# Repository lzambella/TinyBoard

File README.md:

40% keyboard based on a layout I found somewhere, possibly Reddit, and modified for my own tastes. Runs on TMK firmware.

**Switches**
Uses any Cherry full size 5-hole compatible ones. I like to use Gateron North Poles.

LEDs should be 1206 package.

TODO:
* Add STEP files for 3d printing/designing
* PDF files of schematics
* Better docs
* images
* how to build one?

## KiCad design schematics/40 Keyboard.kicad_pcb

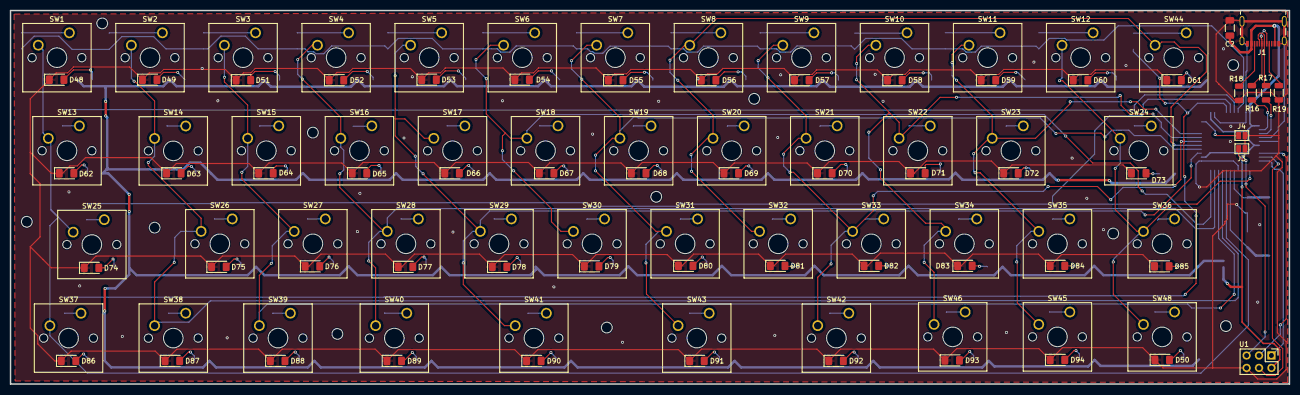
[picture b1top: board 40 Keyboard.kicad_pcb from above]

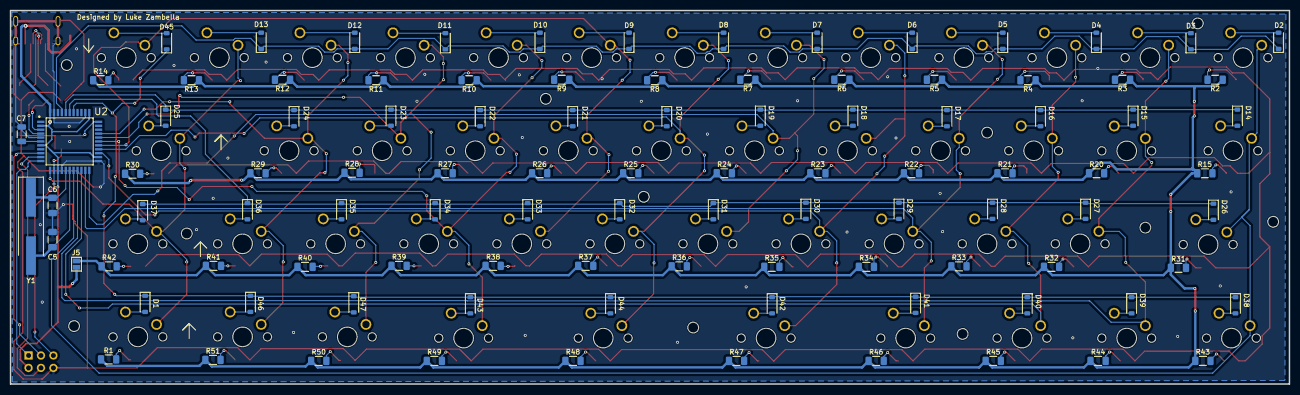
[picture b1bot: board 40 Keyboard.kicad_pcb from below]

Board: 2 copper layers, 261.1 x 76.2 mm, 203 parts (100 on the bottom side), 127 nets.

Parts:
C2: 4.7uF; C_1206_3216Metric_Pad1.33x1.80mm_HandSolder
C5, C6: C1206C220K3HAC7800; C_1206_3216Metric_Pad1.33x1.80mm_HandSolder
C7: 1uF; C_1206_3216Metric
D1, D2, D3, D4, D5, D6, D7, D8, D9, D10, D11, D12, D13, D14, D15, D16, D17, D18, D19, D20, D21, D22, D23, D24, D25, D26, D27, D28, D29, D30, D31, D32, D33, D34, D35, D36, D37, D38, D39, D40, D41, D42, D43, D44, D45, D46, D47: D; D_SOD-123
D48, D49, D50, D51, D52, D53, D54, D55, D56, D57, D58, D59, D60, D61, D62, D63, D64, D65, D66, D67, D68, D69, D70, D71, D72, D73, D74, D75, D76, D77, D78, D79, D80, D81, D82, D83, D84, D85, D86, D87, D88, D89, D90, D91, D92, D93, D94: LED; LED_1206_3216Metric_Pad1.42x1.75mm_HandSolder
J1: 2171790001; MOLEX_2171790001
J3: RESET; SolderJumper-2_P1.3mm_Open_Pad1.0x1.5mm
J4: HWB; SolderJumper-2_P1.3mm_Open_Pad1.0x1.5mm
J5: LED_ENABLE_JUMPER; SolderJumper-2_P1.3mm_Open_Pad1.0x1.5mm
R1, R2, R3, R4, R5, R6, R7, R8, R9, R10, R11, R12, R13, R14, R15, R20, R21, R22, R23, R24, R25, R26, R27, R28, R29, R30, R31, R32, R33, R34, R35, R36, R37, R38, R39, R40, R41, R42, R43, R44, R45, R46, R47, R48, R49, R50, R51: 511; R_1206_3216Metric_Pad1.30x1.75mm_HandSolder
R16, R17: 22; R_1206_3216Metric
R18, R19: 5.1k; R_1206_3216Metric
SW1, SW2, SW3, SW4, SW5, SW6, SW7, SW8, SW9, SW10, SW11, SW12, SW13, SW14, SW15, SW16, SW17, SW18, SW19, SW20, SW21, SW22, SW23, SW24, SW25, SW26, SW27, SW28, SW29, SW30, SW31, SW32, SW33, SW34, SW35, SW36, SW37, SW38, SW39, SW40, SW41, SW42, SW43, SW44, SW45, SW46, SW48: KS-33; Cherry MX switch
U1: PinHeader_2x03_P2.54mm_Vertical
U2: ATMEGA32U4-AU; atmega32u4
Y1: 16Mhz; Crystal_SMD_HC49-SD_HandSoldering

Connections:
32U4_USB_DN: J1.A7 (DN1), J1.B7 (DN2), R16.1
32U4_USB_DP: J1.A6 (DP1), J1.B6 (DP2), R17.1
/LED Circuit/LED_5V: J5.1, R1.1, R2.1, R3.1, R4.1, R5.1, R6.1, R7.1, R8.1, R9.1, R10.1, R11.1, R12.1, R13.1, R14.1, R15.1, R20.1, R21.1, R22.1, R23.1, R24.1, R25.1, R26.1, R27.1, R28.1, R29.1, R30.1, R31.1, R32.1, R33.1, R34.1, R35.1, R36.1, R37.1, R38.1, R39.1, R40.1, R41.1, R42.1, R43.1, R44.1, R45.1, R46.1, R47.1, R48.1, R49.1, R50.1, R51.1
/Matrix/D_C1R1: D2.2 (A), SW1.1
/Matrix/D_C1R2: D14.2 (A), SW13.1
/Matrix/D_C1R3: D26.2 (A), SW25.1
/Matrix/D_C1R4: D38.2 (A), SW37.1
/Matrix/D_C2R1: D3.2 (A), SW2.1
/Matrix/D_C2R2: D15.2 (A), SW14.1
/Matrix/D_C2R3: D27.2 (A), SW26.1
/Matrix/D_C2R4: D39.2 (A), SW38.1
/Matrix/D_C3R1: D4.2 (A), SW3.1
/Matrix/D_C3R2: D16.2 (A), SW15.1
/Matrix/D_C3R3: D28.2 (A), SW27.1
/Matrix/D_C3R4: D40.2 (A), SW39.1
/Matrix/D_C4R1: D5.2 (A), SW4.1
/Matrix/D_C4R2: D17.2 (A), SW16.1
/Matrix/D_C4R3: D29.2 (A), SW28.1
/Matrix/D_C4R4: D41.2 (A), SW40.1
/Matrix/D_C5R1: D6.2 (A), SW5.1
/Matrix/D_C5R2: D18.2 (A), SW17.1
/Matrix/D_C5R3: D30.2 (A), SW29.1
/Matrix/D_C5R4: D42.2 (A), SW41.1
/Matrix/D_C6R1: D7.2 (A), SW6.1
/Matrix/D_C6R2: D19.2 (A), SW18.1
/Matrix/D_C6R3: D31.2 (A), SW30.1
/Matrix/D_C7R1: D8.2 (A), SW7.1
/Matrix/D_C7R2: D20.2 (A), SW19.1
/Matrix/D_C7R3: D32.2 (A), SW31.1
/Matrix/D_C7R4: D44.2 (A), SW43.1
/Matrix/D_C8R1: D9.2 (A), SW8.1
/Matrix/D_C8R2: D21.2 (A), SW20.1
/Matrix/D_C8R3: D33.2 (A), SW32.1
/Matrix/D_C8R4: D45.2 (A), SW44.1
/Matrix/D_C9R1: D10.2 (A), SW9.1
/Matrix/D_C9R2: D22.2 (A), SW21.1
/Matrix/D_C9R3: D34.2 (A), SW33.1
/Matrix/D_C9R4: D43.2 (A), SW42.1
/Matrix/D_C10R1: D11.2 (A), SW10.1
/Matrix/D_C10R2: D23.2 (A), SW22.1
/Matrix/D_C10R3: D35.2 (A), SW34.1
/Matrix/D_C10R4: D47.2 (A), SW46.1
/Matrix/D_C11R1: D12.2 (A), SW11.1
/Matrix/D_C11R2: D24.2 (A), SW23.1
/Matrix/D_C11R3: D36.2 (A), SW35.1
/Matrix/D_C11R4: D46.2 (A), SW45.1
/Matrix/D_C12R1: D13.2 (A), SW12.1
/Matrix/D_C12R2: D25.2 (A), SW24.1
/Matrix/D_C12R3: D37.2 (A), SW36.1
/Matrix/D_C12R4: D1.2 (A), SW48.1
/Microcontroller/XTAL_1: C5.1, U2.17 (XTAL1), Y1.2
/Microcontroller/XTAL_2: C6.1, U2.16 (XTAL2), Y1.1
COL_1: SW1.2, SW13.2, SW25.2, SW37.2, U2.18 (PD0)
COL_2: SW2.2, SW14.2, SW26.2, SW38.2, U2.19 (PD1)
COL_3: SW3.2, SW15.2, SW27.2, SW39.2, U2.20 (PD2)
COL_4: SW4.2, SW16.2, SW28.2, SW40.2, U2.21 (PD3)
COL_5: SW5.2, SW17.2, SW29.2, SW41.2, U2.25 (PD4)
COL_6: SW6.2, SW18.2, SW30.2, U2.22 (PD5)
COL_7: SW7.2, SW19.2, SW31.2, SW43.2, U2.26 (PD6)
COL_8: SW8.2, SW20.2, SW32.2, SW44.2, U2.27 (PD7)
COL_9: SW9.2, SW21.2, SW33.2, SW42.2, U2.28 (PB4)
COL_10: SW10.2, SW22.2, SW34.2, SW46.2, U2.29 (PB5)
COL_11: SW11.2, SW23.2, SW35.2, SW45.2, U2.30 (PB6)
COL_12: SW12.2, SW24.2, SW36.2, SW48.2, U2.12 (PB7)
GND: C2.2, C5.2, C6.2, C7.2, D48.1 (K), D49.1 (K), D50.1 (K), D51.1 (K), D52.1 (K), D53.1 (K), D54.1 (K), D55.1 (K), D56.1 (K), D57.1 (K), D58.1 (K), D59.1 (K), D60.1 (K), D61.1 (K), D62.1 (K), D63.1 (K), D64.1 (K), D65.1 (K), D66.1 (K), D67.1 (K), D68.1 (K), D69.1 (K), D70.1 (K), D71.1 (K), D72.1 (K), D73.1 (K), D74.1 (K), D75.1 (K), D76.1 (K), D77.1 (K), D78.1 (K), D79.1 (K), D80.1 (K), D81.1 (K), D82.1 (K), D83.1 (K), D84.1 (K), D85.1 (K), D86.1 (K), D87.1 (K), D88.1 (K), D89.1 (K), D90.1 (K), D91.1 (K), D92.1 (K), D93.1 (K), D94.1 (K), J1.A1B12 (GND1), J1.B1A12 (GND2), J1.SH1 (SHIELD1), J1.SH2 (SHIELD2), J1.SH3 (SHIELD3), J1.SH4 (SHIELD4), J3.1, J4.2, R18.2, R19.2, U1.6 (GND), U2.5 (UGND), U2.15 (GND), U2.23 (GND), U2.35 (GND), U2.43 (GND)
MISO: U1.1 (MISO), U2.11 (PB3)
MOSI: U1.4 (MOSI), U2.10 (PB2)
unnamed: D48.2 (A), R2.2
unnamed: D49.2 (A), R3.2
unnamed: D50.2 (A), R1.2
unnamed: D51.2 (A), R4.2
unnamed: D52.2 (A), R5.2
unnamed: D53.2 (A), R6.2
unnamed: D54.2 (A), R7.2
unnamed: D55.2 (A), R8.2
unnamed: D56.2 (A), R9.2
unnamed: D57.2 (A), R10.2
unnamed: D58.2 (A), R11.2
unnamed: D59.2 (A), R12.2
unnamed: D60.2 (A), R13.2
unnamed: D61.2 (A), R14.2
unnamed: D62.2 (A), R15.2
unnamed: D63.2 (A), R20.2
unnamed: D64.2 (A), R21.2
unnamed: D65.2 (A), R22.2
unnamed: D66.2 (A), R23.2
unnamed: D67.2 (A), R24.2
unnamed: D68.2 (A), R25.2
unnamed: D69.2 (A), R26.2
unnamed: D70.2 (A), R27.2
unnamed: D71.2 (A), R28.2
unnamed: D72.2 (A), R29.2
unnamed: D73.2 (A), R30.2
unnamed: D74.2 (A), R31.2
unnamed: D75.2 (A), R32.2
unnamed: D76.2 (A), R33.2
unnamed: D77.2 (A), R34.2
unnamed: D78.2 (A), R35.2
unnamed: D79.2 (A), R36.2
unnamed: D80.2 (A), R37.2
unnamed: D81.2 (A), R38.2
unnamed: D82.2 (A), R39.2
unnamed: D83.2 (A), R40.2
unnamed: D84.2 (A), R41.2
unnamed: D85.2 (A), R42.2
unnamed: D86.2 (A), R43.2
unnamed: D87.2 (A), R44.2
unnamed: D88.2 (A), R45.2
unnamed: D89.2 (A), R46.2
unnamed: D90.2 (A), R47.2
unnamed: D91.2 (A), R48.2
unnamed: D92.2 (A), R49.2
unnamed: D93.2 (A), R50.2
unnamed: D94.2 (A), R51.2
unnamed: J1.A5 (CC1), R19.1
unnamed: J1.B5 (CC2), R18.1
unnamed: R17.2, U2.4 (D+)
unnamed: R16.2, U2.3 (D-)
unnamed: J4.1, U2.33 (PE2)
unnamed: C7.1, U2.6 (UCAP)
ROW_1: D2.1 (K), D3.1 (K), D4.1 (K), D5.1 (K), D6.1 (K), D7.1 (K), D8.1 (K), D9.1 (K), D10.1 (K), D11.1 (K), D12.1 (K), D13.1 (K), U2.41 (PF0)
ROW_2: D14.1 (K), D15.1 (K), D16.1 (K), D17.1 (K), D18.1 (K), D19.1 (K), D20.1 (K), D21.1 (K), D22.1 (K), D23.1 (K), D24.1 (K), D25.1 (K), U2.40 (PF1)
ROW_3: D26.1 (K), D27.1 (K), D28.1 (K), D29.1 (K), D30.1 (K), D31.1 (K), D32.1 (K), D33.1 (K), D34.1 (K), D35.1 (K), D36.1 (K), D37.1 (K), U2.39 (PF4)
ROW_4: D1.1 (K), D38.1 (K), D39.1 (K), D40.1 (K), D41.1 (K), D42.1 (K), D43.1 (K), D44.1 (K), D45.1 (K), D46.1 (K), D47.1 (K), U2.38 (PF5)
RSET: J3.2, U1.5 (RSET), U2.13 (~RESET)
SCK: U1.3 (SCK), U2.9 (PB1)
USB_VBUS_5: C2.1, J1.A4B9 (VBUS1), J1.B4A9 (VBUS2), J5.2, U1.2 (VCC), U2.2 (UVCC), U2.7 (VBUS), U2.14 (VCC), U2.24 (AVCC), U2.34 (VCC), U2.44 (AVCC)

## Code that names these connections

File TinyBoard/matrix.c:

#include <stdint.h>
#include <stdbool.h>
#include <avr/io.h>
#include <util/delay.h>
#include "matrix.h"
#include "debug.h"
#include "config.h"

// Variable to store the current row
static uint8_t debouncing = DEBOUNCE;

static matrix_row_t matrix[MATRIX_ROWS];
static matrix_row_t matrix_debouncing[MATRIX_ROWS];

// Function definitions
static matrix_row_t read_cols(void);
static void unselect_rows(void);
static void select_row(uint8_t row);

void matrix_init(void) {
    MCUCR |= (1<<JTD);
    MCUCR |= (1<<JTD);

    // Set row pins to output
    // PORF 0,1,4,5 >> ROW 1,2,3,4
    DDRF |= (1 << 0);
    DDRF |= (1 << 1);
    DDRF |= (1 << 4);
    DDRF |= (1 << 5);

    // Initialize all rows to HIGH
    PORTF |= (1 << PF0);
    PORTF |= (1 << PF1);
    PORTF |= (1 << PF4);
    PORTF |= (1 << PF5);
    
    // Set column pins as input
    DDRD &= ~(1 << 0); // col 1
    DDRD &= ~(1 << 1); // 2
    DDRD &= ~(1 << 2); // 3
    DDRD &= ~(1 << 3); // 4
    DDRD &= ~(1 << 4); // 5
    DDRD &= ~(1 << 5); // 6
    DDRD &= ~(1 << 6); // 7
    DDRD &= ~(1 << 7); // 8

    DDRB &= ~(1 << 4); // 9
    DDRB &= ~(1 << 5); // 10
    DDRB &= ~(1 << 6); // 11
    DDRB &= ~(1 << 7); // 12

    // Enable internal pullups
    PORTD |= (1 << 0); // col 1
    PORTD |= (1 << 1); // 2
    PORTD |= (1 << 2); // 3
    PORTD |= (1 << 3); // 4
    PORTD |= (1 << 4); // 5
    PORTD |= (1 << 5); // 6
    PORTD |= (1 << 6); // 7
    PORTD |= (1 << 7); // 8

    PORTB |= (1 << 4); // 9
    PORTB |= (1 << 5); // 10
    PORTB |= (1 << 6); // 11
    PORTB |= (1 << 7); // 12

    // make sure matrix is cleared on init
    for (int i = 0; i < MATRIX_ROWS; i++) { 
        matrix[i] = 0;
        matrix_debouncing[i] = 0;
    }
}

uint8_t matrix_scan(void) {
    debug("Scan row\n");
    for (uint8_t i = 0; i < MATRIX_ROWS; i++) {
        select_row(i);
        _delay_us(100);  // without this wait read unstable value.
        matrix_row_t cols = read_cols();
        if (matrix_debouncing[i] != cols) {
            matrix_debouncing[i] = cols;
            if (debouncing) {
                debug("bounce!: "); debug_hex(debouncing); debug("\n");
            }
            debouncing = DEBOUNCE;
        }
        unselect_rows();
    }

    if (debouncing) {
        if (--debouncing) {
            _delay_ms(1);
        } else {
            for (uint8_t i = 0; i < MATRIX_ROWS; i++) {
                matrix[i] = matrix_debouncing[i];
            }
        }
    }

    return 1;
}

/*
* Deselects rows by writing a HIGH to all the row pins
*/
static void unselect_rows(void)
{
    PORTF |= (1 << PF0);
    PORTF |= (1 << PF1);
    PORTF |= (1 << PF4);
    PORTF |= (1 << PF5);
}

/*
* Get a single row in the matrix array
* Each row contains bits that represent the columns in the matrix
*/
matrix_row_t matrix_get_row(uint8_t row)
{
    return matrix[row];
}

/*
* Reads all of the columns into an integer
*/
static matrix_row_t read_cols()
{
    // Get the state of the columns

    // If we read a LOW at the pin input (switch pressed) we want the variable to be HIGH
    uint16_t c1 =  ((~PIND & (1 << PIND0)) >> PIND0);
    uint16_t c2 =  ((~PIND & (1 << PIND1)) >> PIND1);
    uint16_t c3 =  ((~PIND & (1 << PIND2)) >> PIND2);
    uint16_t c4 =  ((~PIND & (1 << PIND3)) >> PIND3);
    uint16_t c5 =  ((~PIND & (1 << PIND4)) >> PIND4);
    uint16_t c6 =  ((~PIND & (1 << PIND5)) >> PIND5);
    uint16_t c7 =  ((~PIND & (1 << PIND6)) >> PIND6);
    uint16_t c8 =  ((~PIND & (1 << PIND7)) >> PIND7);

    uint16_t c9 =  ((~PINB & (1 << PINB4)) >> PINB4);
    uint16_t c10 = ((~PINB & (1 << PINB5)) >> PINB5);
    uint16_t c11 = ((~PINB & (1 << PINB6)) >> PINB6);
    uint16_t c12 = ((~PINB & (1 << PINB7)) >> PINB7);

    // Make a continuous integer of the inputs
    matrix_row_t C = 0;

    C = C | c1  << 0;
    C = C | c2  << 1;
    C = C | c3  << 2;
    C = C | c4  << 3;
    C = C | c5  << 4;
    C = C | c6  << 5;
    C = C | c7  << 6;
    C = C | c8  << 7;
    C = C | c9  << 8;
    C = C | c10 << 9;
    C = C | c11 << 10;
    C = C | c12 << 11;

    debug_bin16(C); debug("\n");
    return C;
}

/**
 * Select a row by writing LOW to it
*/
static void select_row(uint8_t row)
{
    switch (row) {
        // Row 1 (pin F0)
        case 0:
            DDRF |= (1 << DDF0);
            PORTF &= ~(1 << PF0); 
            break;
        case 1:
        // Row 2 (pin F1)
            DDRF |= (1 << DDF1);
            PORTF &= ~(1 << PF1); 
            break;
        case 2:
        // Row 3 (Pin F4)
            DDRF |= (1 << DDF4);
            PORTF &= ~(1 << PF4);
            break;
        case 3:
        // Row 4 (Pin F5)
            DDRF |= (1 << DDF5);
            PORTF &= ~(1 << PF5); 
            break;
    }
}

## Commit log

2024-04-14 Fix keymapping
2024-04-14 update gitignore
2024-04-19 Update key layout, increase debounce, PCB update
2024-05-03 Update schematic and board layout
2025-02-01 Update project to use Rev2 final board
2025-02-06 Update firmware
